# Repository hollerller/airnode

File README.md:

# AirNode

> Open-source environmental IoT sensor — air quality monitoring with a full-stack mobile experience.

---

## What is AirNode?

AirNode is a low-power environmental sensor that measures air quality in real time and streams data to a mobile app via BLE. The app acts as a gateway, forwarding sensor data to a cloud backend over HTTP.

It is designed as a complete end to end IoT product, from embedded firmware to cloud backend to cross-platform mobile app.

---

## Features

- 🌡️ Temperature, humidity and pressure (BME680)
- 💨 PM1.0, PM2.5 and PM10 particulate matter (PMSA003I)
- 📱 Android app — real-time dashboard, historical charts, device config
- 🔵 BLE connection — scan, connect, and read sensor data in real time
- ☁️ Cloud backend with auth, device registry, and data storage
- 🔋 Ultra low-power design — ~15 µA average current at 5-min intervals
- 🔧 Custom PCB hardware design (KiCad)
- 🔄 OTA firmware updates

---

## Architecture

```
┌─────────────────────────────────────────┐
│              AIRNODE DEVICE             │
│         nRF52840 + Zephyr RTOS          │
│      BME680 (I2C) · PMSA003I (I2C)      │
└──────────────────┬──────────────────────┘
                   │ BLE (notify)
                   ▼
┌─────────────────────────────────────────┐
│           MOBILE APP (Gateway)          │
│        React Native · TypeScript        │
│   BLE scan → connect → read → display  │
│          HTTP POST → Backend            │
└──────────────────┬──────────────────────┘
                   │ HTTPS
                   ▼
┌─────────────────────────────────────────┐
│              BACKEND                    │
│         NestJS · PostgreSQL             │
│    Auth · Device Registry · Readings    │
└─────────────────────────────────────────┘
```

---

## Tech Stack

| Layer          | Technology                           |
| -------------- | ------------------------------------ |
| Firmware       | C · Zephyr RTOS · nRF Connect SDK    |
| Protocols      | BLE 5.0 · I2C                        |
| Mobile         | React Native · TypeScript            |
| Backend        | NestJS · PostgreSQL                  |
| Infrastructure | Fly.io · GitHub Actions · Cloudflare |

---

## Project Structure

```
airnode/
├── firmware/          # nRF52 firmware (C/C++ + Zephyr)
├── apps/
│   ├── mobile/        # React Native app (iOS + Android)
│   └── backend/       # NestJS REST API + MQTT
├── docs/              # Architecture, BLE profile, API reference
└── hardware/          # Schematics and BOM
```

---

## Status

This project is currently in active development. Follow the progress through commits.

| Phase            | Description                 | Status         |
| ---------------- | --------------------------- | -------------- |
| Firmware Phase 1 | MCU Low Power               | ✅ Complete    |
| Firmware Phase 2 | BME680 sensor               | ✅ Complete    |
| Firmware Phase 3 | BLE Minimal                 | ✅ Complete    |
| Firmware Phase 4 | PMSA003I sensor             | ✅ Complete    |
| Firmware Phase 5 | System Integration          | ✅ Complete    |
| Backend          | Auth + Device Registry      | ✅ Complete    |
| Mobile App       | Auth + BLE Provisioning     | ✅ Complete    |
| Data Pipeline    | App → HTTP → Backend → DB   | ✅ Complete    |
| Dashboard        | Historical data + Charts    | ✅ Complete    |
| Device Config    | Settings API + BLE commands | 🔄 In progress |
| MVP Demo         | End-to-end working product  | ⚪ Pending     |
| Hardware         | Custom PCB (KiCad)          | ⚪ Pending     |

---

## Getting Started

Documentation and setup guides coming soon as each phase is completed.

---

## Author

Built by [@hollerller](https://github.com/hollerller)

---

_AirNode — breathing intelligence into air quality monitoring._

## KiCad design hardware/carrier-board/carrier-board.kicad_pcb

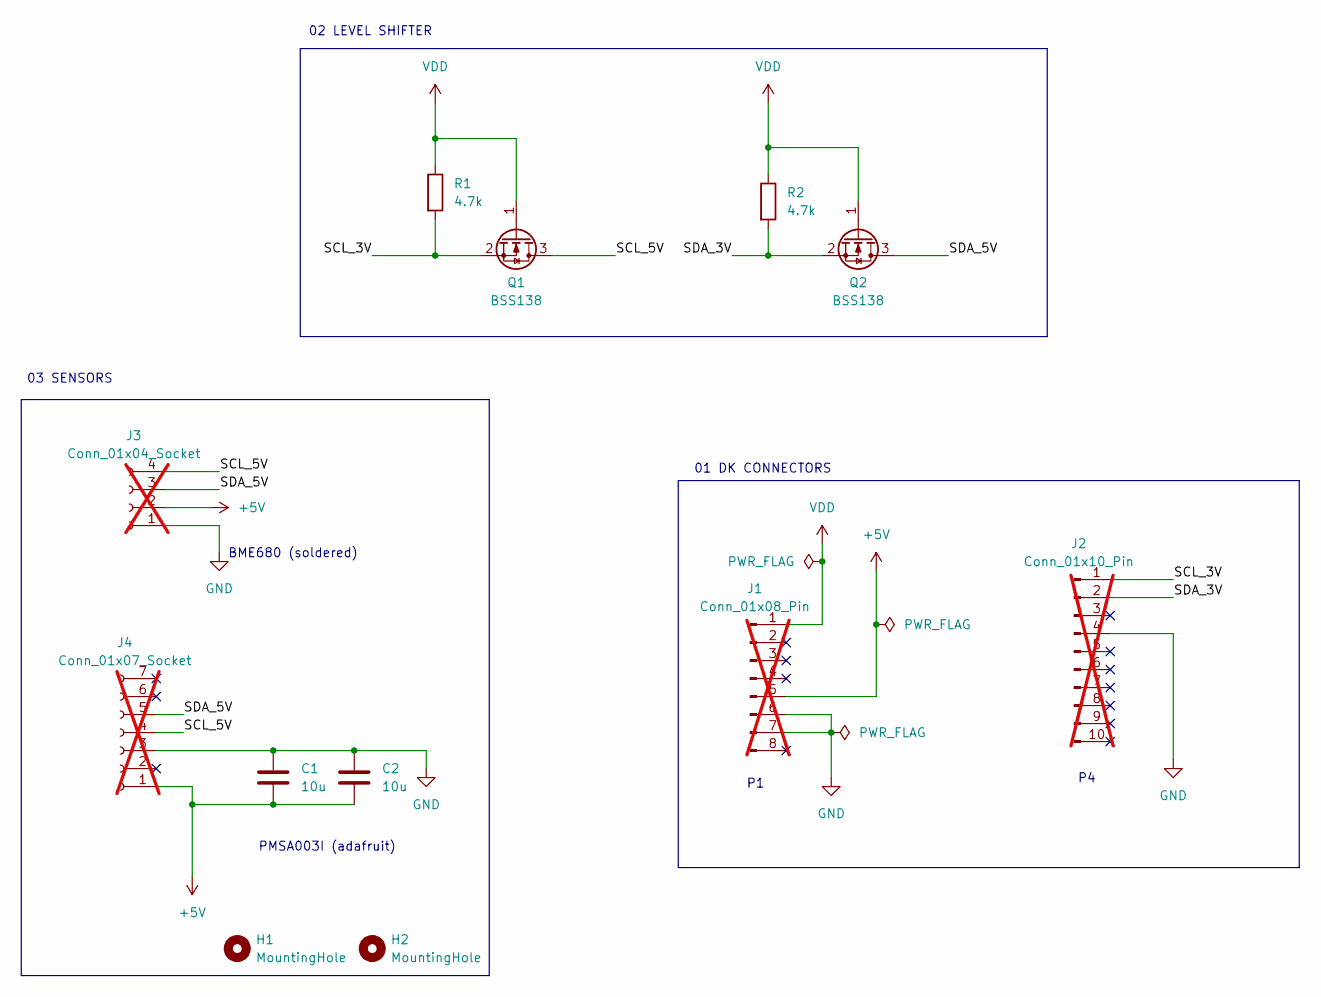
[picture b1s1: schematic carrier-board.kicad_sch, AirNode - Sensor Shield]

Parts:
C1, C2: 10u; C_0805_2012Metric; LCSC C15850
H1, H2: MountingHole; MountingHole_2.7mm_M2.5
J1: Conn_01x08_Pin; PinHeader_1x08_P2.54mm_Vertical; not fitted
J2: Conn_01x10_Pin; PinHeader_1x10_P2.54mm_Vertical; not fitted
J3: Conn_01x04_Socket; PinSocket_1x04_P2.54mm_Vertical; not fitted
J4: Conn_01x07_Socket; PinSocket_1x07_P2.54mm_Vertical; not fitted
Q1, Q2: BSS138; SOT-23; LCSC C75547
R1, R2: 4.7k; R_0805_2012Metric; LCSC C17673

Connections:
+5V: C1.2, C2.2, J1.5, J3.2, J4.1
/SCL_3V: J2.1, Q1.2 (S), R1.2
/SCL_5V: J3.4, J4.4, Q1.3 (D)
/SDA_3V: J2.2, Q2.2 (S), R2.2
/SDA_5V: J3.3, J4.5, Q2.3 (D)
GND: C1.1, C2.1, J1.6, J1.7, J2.4, J3.1, J4.3
VDD: J1.1, Q1.1 (G), Q2.1 (G), R1.1, R2.1

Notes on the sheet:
03 SENSORS
02 LEVEL SHIFTER
BME680 (soldered)
01 DK CONNECTORS
PMSA003I (adafruit)

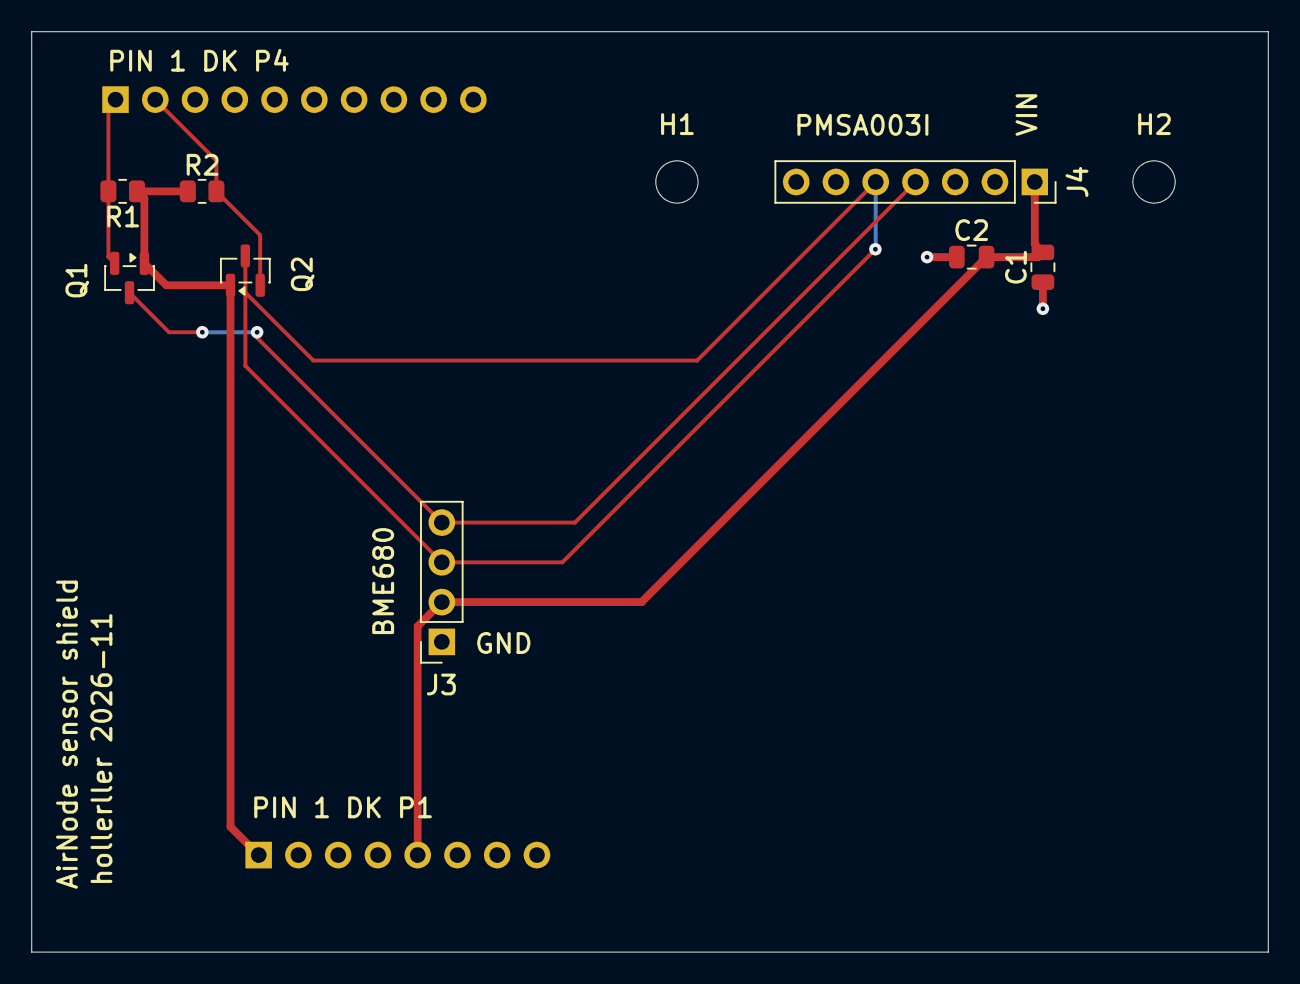
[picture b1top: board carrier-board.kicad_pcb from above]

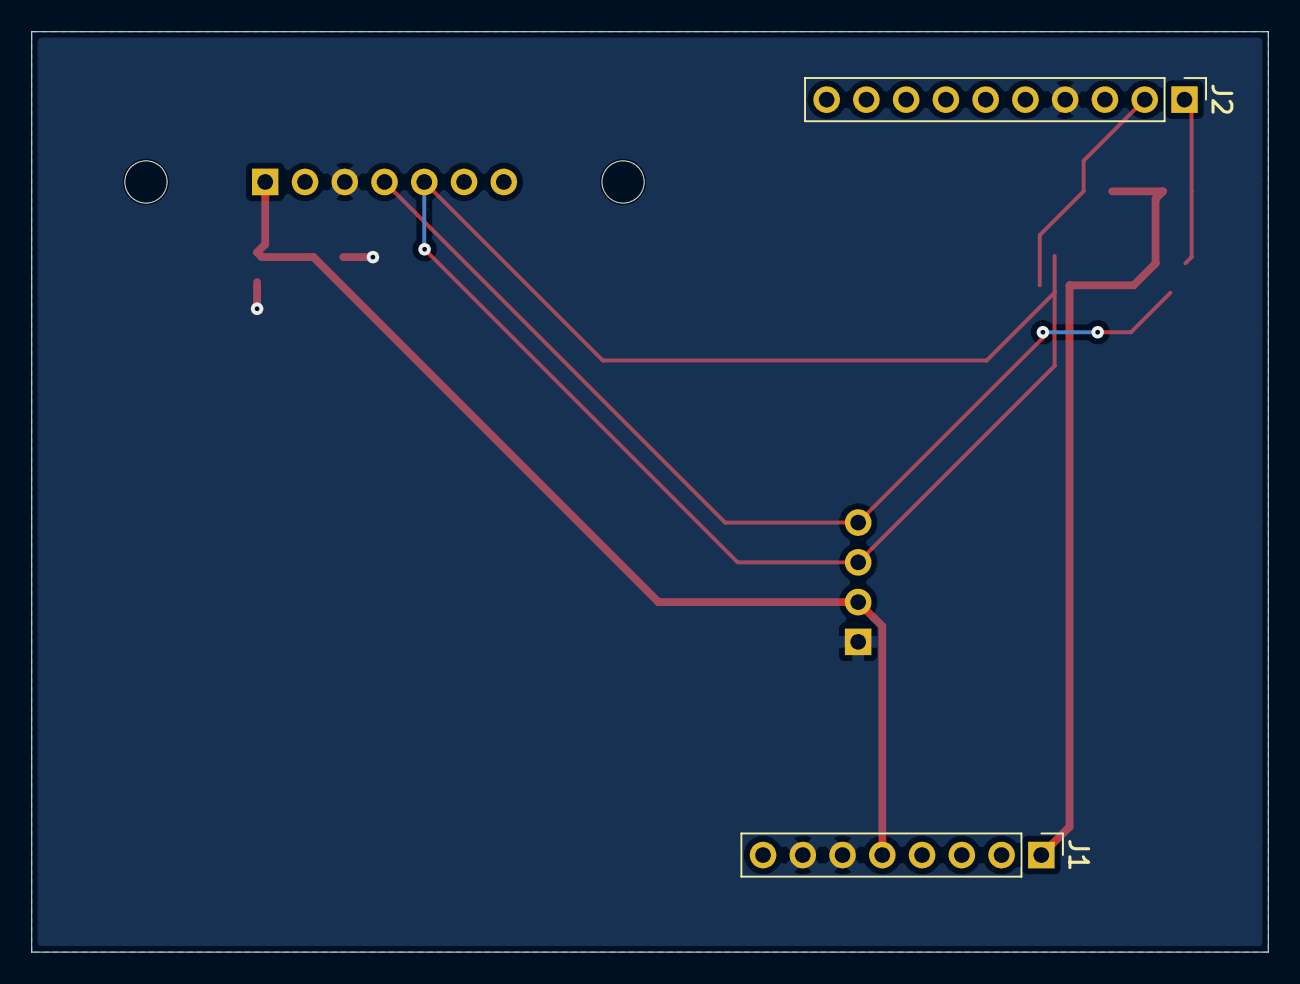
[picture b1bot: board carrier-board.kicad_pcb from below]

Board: 2 copper layers, 79.0 x 58.8 mm, 12 parts (2 on the bottom side), 7 nets.

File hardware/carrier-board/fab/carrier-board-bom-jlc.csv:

Comment,Designator,Footprint,LCSC Part #
4.7k,"R1,R2",0805,C17673
BSS138,"Q1,Q2",SOT-23,C75547
10uF,"C1,C2",0805,C15850

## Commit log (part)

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2026-02-27 feat: initial project structure and README
2026-02-28 feat(modulo-0): 0.1.1 and 0.1.2 done
2026-02-28 feat(modulo-0): 0.1.3/4/5/6 done
2026-02-28 feat(modulo-0): integration practice done
2026-03-01 feat(modulo-0): complete 0.2.1
2026-03-01 feat(modulo-0): 0.2.2 done
2026-03-01 feat(modulo-0) 0.2.3 done
2026-03-01 feat(modulo-0) 0.2.4 done
2026-03-01 feat(modulo-0): complete 0.2 ts
2026-03-01 feat(modulo-0): complete 0.3 - React
2026-03-04 feat(fase-1): project config
2026-03-04 feat(fase-1): power management and low power testing
2026-03-04 rtc wake up timer
2026-03-06 feat(fase-2): add BME680 overlay and prj.conf for I2C sensor
2026-03-07 feat(fase-2): bme680 sensor reading temp, hum, press
2026-03-07 feat(fase-2): decrease pressure oversampling to reduce consumption
2026-03-10 feat(fase-1): measure sleep current 2.37uA
    - Disabled UART console via Kconfig
    - k_sleep() 10s wake interval with led toggle
    - Sleep current 1.79uA avg, 4.17uA max
    - DoD achieved: <10uA
2026-03-13 feat(fase-3): airnode connected via bluetooth
2026-03-15 feat(fase-3): read value from ble
2026-03-15 feat(fase-3): send changing values via BLE notify
2026-03-15 feat(fase-3): notify temperature data over ble
2026-03-17 feat(fase-4): build pmsa003i driver and test raw readings
2026-03-17 refactor(fase-4): add static to variables, change initialization order, fix checksum validation, general error review
2026-03-21 feat(fase-4): set warm up time and NACK/timeout with retry
2026-03-21 refactor(fase-4): evaluate start characters
2026-03-21 feat(fase-5): store sensor data in struct
2026-03-21 feat(fase-5): send sensor data periodically using sig environmental sensor service
2026-03-21 feat(fase-5): disable logs to measure current and fsm diagram
2026-03-21 feat(fase-5): fsm
2026-03-21 feat(fase-6): create nestjs repo and first testing
2026-03-21 feat(fase-6): create Devices and Readings resources
2026-03-21 feat(fase-6): device and readings dto and entitiy definition
2026-03-21 feat(fase-6): implement get and post for reading and devices
2026-03-21 feat(fase-6): add env variables and connect to postgresql
2026-03-21 feat(fase-6): implement crud connected with db
2026-03-21 feat(fase-6): add docker compose with postgresql, redis and influxdb images
2026-03-21 feat(fase-6): add mqtt broker emqx and dashboard
2026-03-22 feat(fase-6): add users entity and register users
2026-03-22 feat(fase-6): handle user login and JWT token
2026-03-22 feat(fase-6): implement api to refresh jwt token
2026-03-22 feat(fase-6): add guard to restrict routes and create public decorator
2026-03-25 feat(fase-6): get user_id, create realtion between users and devices and add device token
2026-03-28 docs: update README to reflect current project status
2026-03-29 feat(fase-6): finish device crud
2026-03-29 feat(fase-6): add endpoint to update device status from device
2026-03-29 feat(fase-6): MQTT model doc for airnode
2026-03-29 feat(fase-7): initialize expo project with EAS build
2026-03-29 refactor(fase-7): restructure app directory
2026-03-31 feat(fase-7): add screens with auth stack and tabs
2026-03-31 feat(fase-7): add zustand auth and device stores
2026-04-12 feat(fase-7): add axios instance with token interceptor and react query setup
2026-04-13 feat(fase-7): add login screen with auth service
2026-04-19 add login, logout and register funcionality with backend integration
2026-04-19 add persistent with securestore
2026-04-19 feat(fase-7): add ble permission, scan and print devices
2026-04-19 feat(fase-7): add ble connection, service discovery and sensor data reading
2026-04-21 feat(fase-7): decode and display sensor readings in real time
2026-04-23 feat(fase-7): show connected devices and add disconnect function
2026-04-25 feat(fase-7): clean up code, remove debug logs and ess service lookup
2026-05-04 feat(fase-8): get readings endpoints with date and limit filter
2026-05-19 wip(fase-8): post readings to backend
2026-05-21 feat(fase-8): post bluetooth readings to backend automatically
2026-05-21 docs(fase-8): update readme
2026-05-22 feat(fase-9): query readings from backend to display in app
2026-05-26 feat(fase-9): add temperature chart in app dashboard
2026-06-07 feat(fase-9): add temp line chart with axis

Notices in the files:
README.md:
License: All Rights Reserved
